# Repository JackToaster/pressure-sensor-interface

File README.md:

# Pressure Sensor Interface

This repository contains PCB designs & firmware (WIP) for an 8-channel USB pressure sensor/solenoid valve driver.

## Features

(Note that this is still in the early prototype stage so these specs have not been validated yet)

**8x pressure sensors**

- using the LWPxxx series of low-cost piezoresistive pressure sensors
- HX711 Load cell amplifier to read output
  - Note the full scale range of the pressure sensor is wider than the input range of the HX711 - This means the full range of the sensor may be impossible to read, but this is an acceptable tradeoff for the extremely low cost.
  - Capable of up to 144Hz sampling rate
 
**8x Solenoid Valve Drivers**

- Low-side NMOS switches
- Capable of ~4A per channel
- Separate DC power input for solenoid valves, supports 0-24VDC (Limited by 30V Vds rating of FET)
- Individual PWM control of each channel

**STM32F103 Microcontroller + USB-C**
idk

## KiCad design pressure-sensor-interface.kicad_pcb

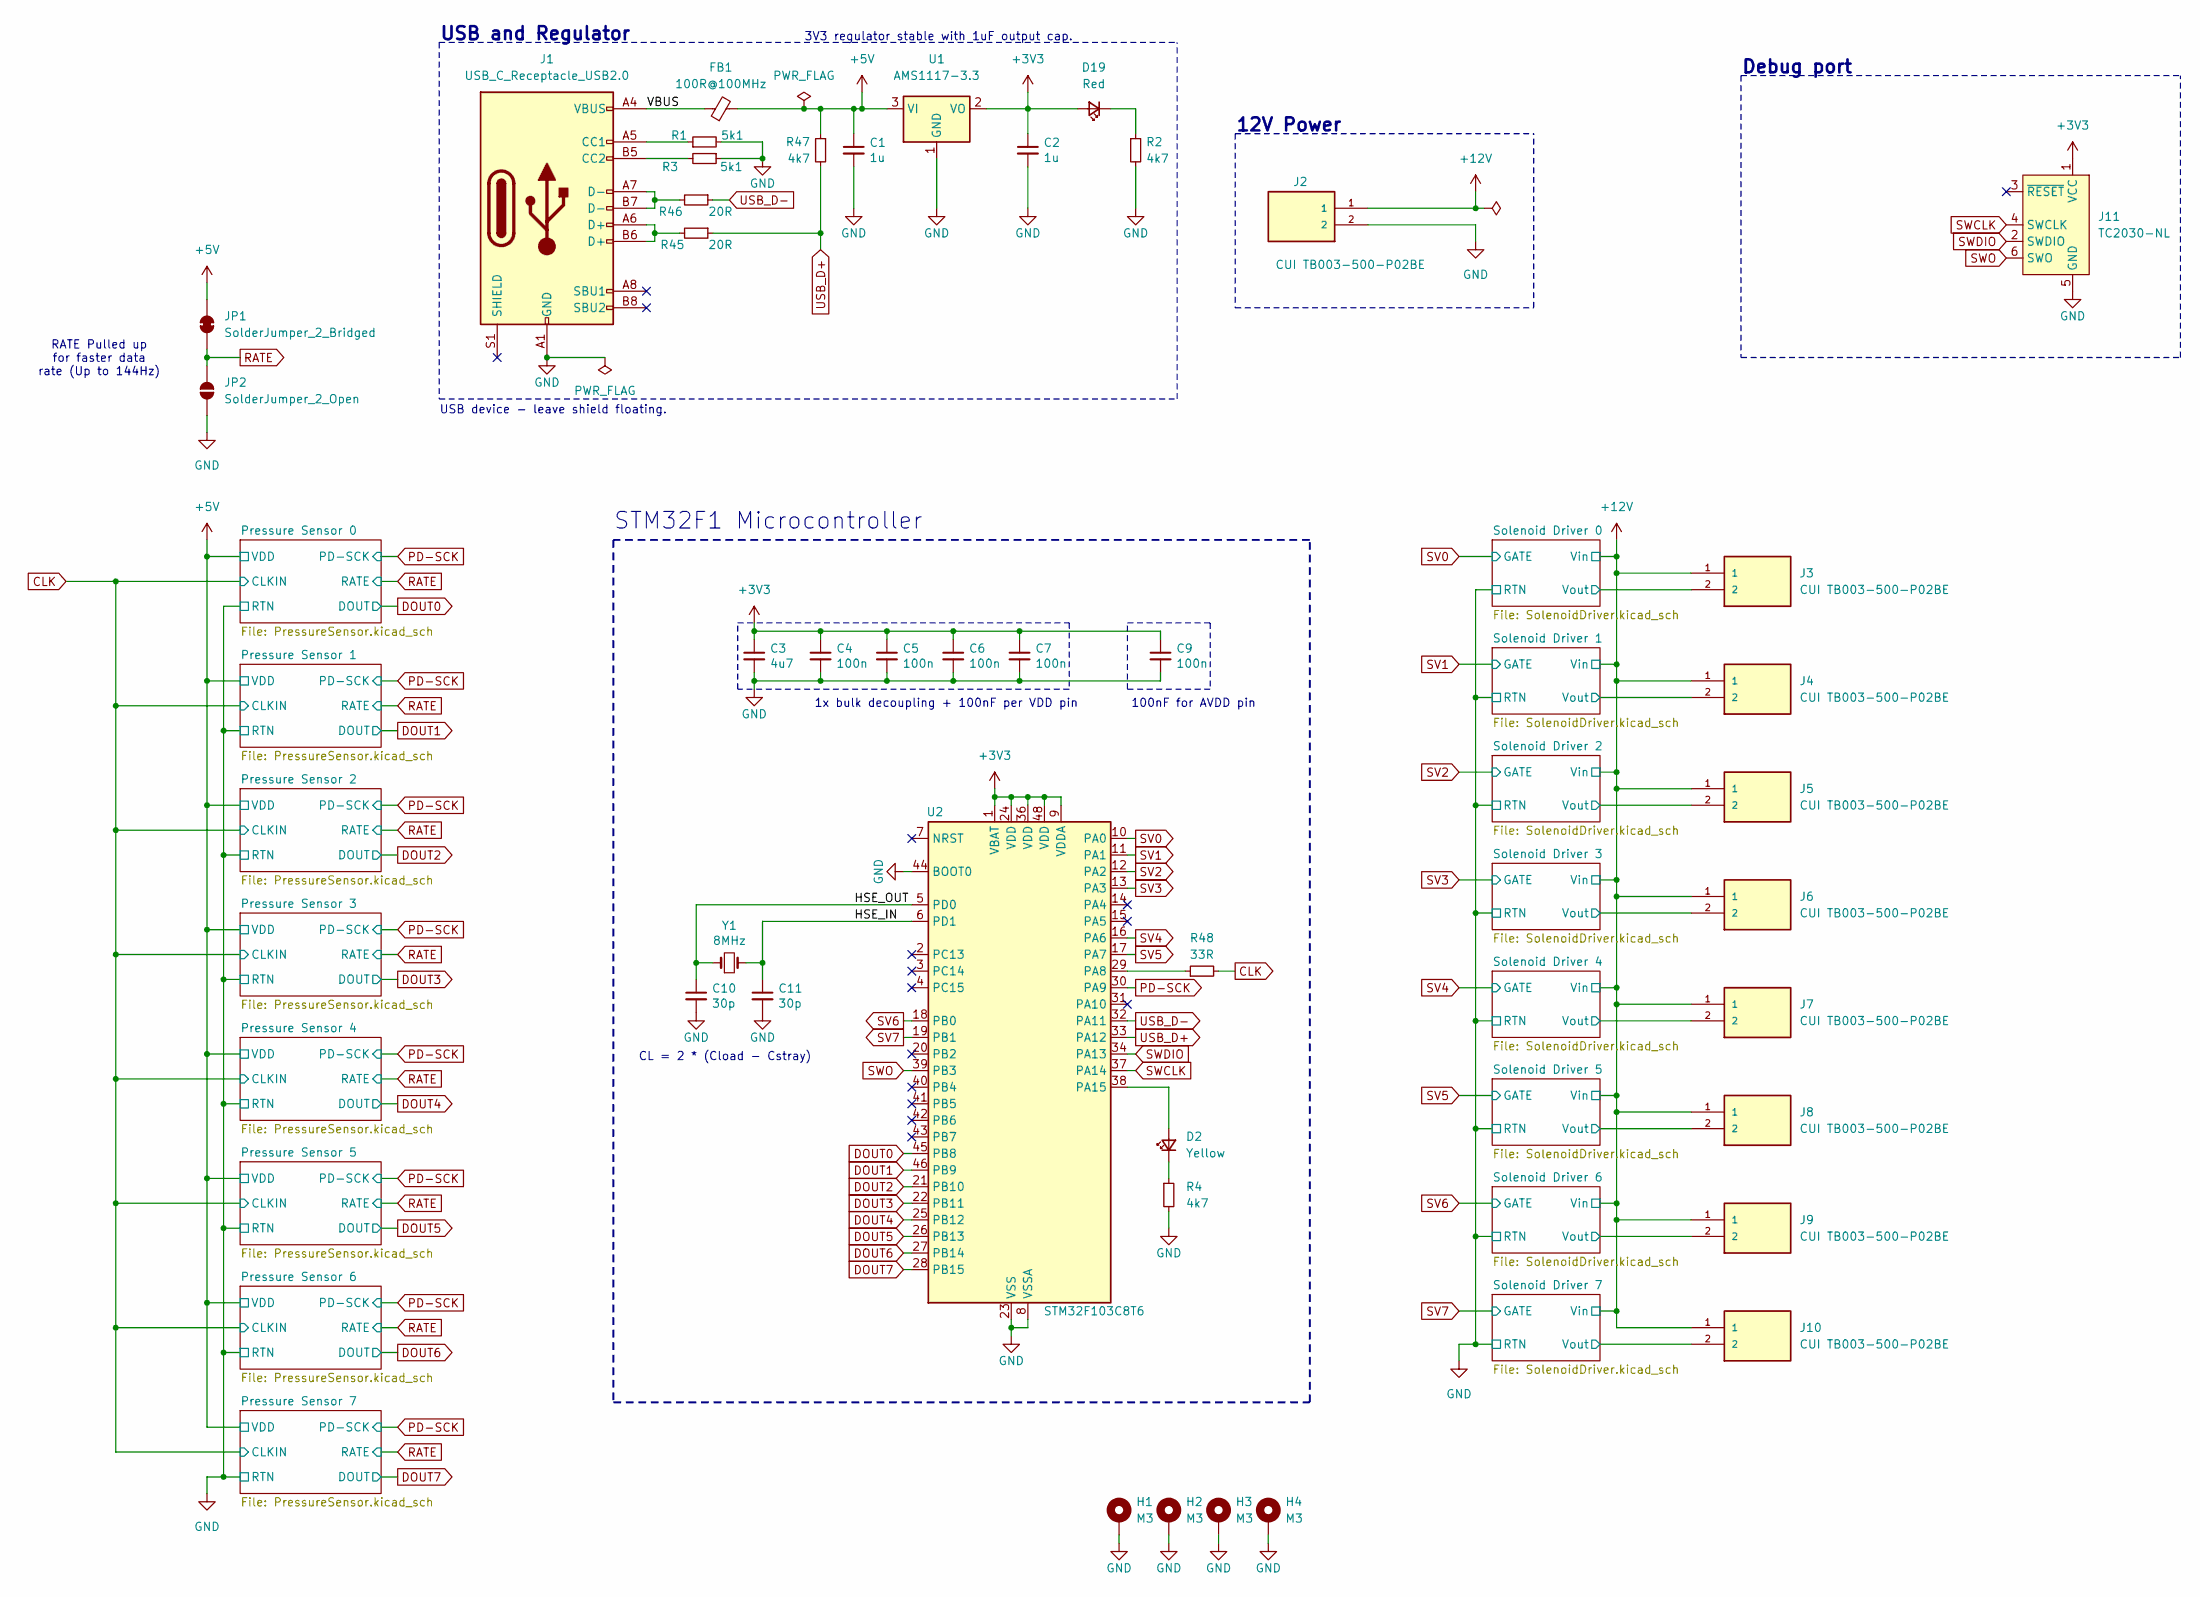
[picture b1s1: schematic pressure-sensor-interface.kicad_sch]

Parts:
C1, C2: 1u; C_0603_1608Metric; LCSC C15849
C3: 4u7; C_0603_1608Metric; LCSC C19666
C4, C5, C6, C7, C9: 100n; C_0603_1608Metric; LCSC C307331
C10, C11: 30p; C_0603_1608Metric; LCSC C1570
D2: Yellow; LED_0603_1608Metric
D19: Red; LED_0603_1608Metric
FB1: 100R@100MHz; R_0805_2012Metric; LCSC C1015
H1, H2, H3, H4: M3; MountingHole_2.2mm_M2_Pad_Via
J1: USB_C_Receptacle_USB2.0; USB_C_Receptacle_HRO_TYPE-C-31-M-12; LCSC C165948
J2, J3, J4, J5, J6, J7, J8, J9, J10: CUI TB003-500-P02BE; CUI_TB003-500-P02BE
J11: TC2030-NL; Tag-Connect_TC2030-IDC-NL_2x03_P1.27mm_Vertical
JP1: SolderJumper_2_Bridged; SolderJumper-2_P1.3mm_Bridged_Pad1.0x1.5mm
JP2: SolderJumper_2_Open; SolderJumper-2_P1.3mm_Open_TrianglePad1.0x1.5mm
R1, R3: 5k1; R_0603_1608Metric; LCSC C25905
R2, R4, R47: 4k7; R_0603_1608Metric
R45, R46: 20R; R_0603_1608Metric; LCSC C25905
R48: 33R; R_0603_1608Metric
U1: AMS1117-3.3; SOT-223-3_TabPin2; LCSC C6186
U2: STM32F103C8T6; LQFP-48_7x7mm_P0.5mm; LCSC C77994
Y1: 8MHz; Crystal_SMD_5032-2Pin_5.0x3.2mm; LCSC C115962

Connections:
+3V3: C2.1, C3.1, C4.1, C5.1, C6.1, C7.1, C9.1, D19.2 (A), J11.1 (VCC), U1.2 (VO), U2.1 (VBAT), U2.9 (VDDA), U2.24 (VDD), U2.36 (VDD), U2.48 (VDD)
+5V: C1.1, FB1.2, JP1.2 (B), R47.1, U1.3 (VI); also elsewhere on the board
+12V: J2.1, J3.1, J4.1, J5.1, J6.1, J7.1, J8.1, J9.1, J10.1; also elsewhere on the board
/HSE_IN: C11.1, U2.6 (PD1), Y1.2
/HSE_OUT: C10.1, U2.5 (PD0), Y1.1
/Solenoid Driver 0/Vout: J3.2; also elsewhere on the board
/Solenoid Driver 1/Vout: J4.2; also elsewhere on the board
/Solenoid Driver 2/Vout: J5.2; also elsewhere on the board
/Solenoid Driver 3/Vout: J6.2; also elsewhere on the board
/Solenoid Driver 4/Vout: J7.2; also elsewhere on the board
/Solenoid Driver 5/Vout: J8.2; also elsewhere on the board
/Solenoid Driver 6/Vout: J9.2; also elsewhere on the board
/Solenoid Driver 7/Vout: J10.2; also elsewhere on the board
/VBUS: FB1.1, J1.A4 (VBUS), J1.A9 (VBUS), J1.B4 (VBUS), J1.B9 (VBUS)
CLK: R48.2; also elsewhere on the board
DOUT0: U2.45 (PB8); also elsewhere on the board
DOUT1: U2.46 (PB9); also elsewhere on the board
DOUT2: U2.21 (PB10); also elsewhere on the board
DOUT3: U2.22 (PB11); also elsewhere on the board
DOUT4: U2.25 (PB12); also elsewhere on the board
DOUT5: U2.26 (PB13); also elsewhere on the board
DOUT6: U2.27 (PB14); also elsewhere on the board
DOUT7: U2.28 (PB15); also elsewhere on the board
GND: C1.2, C2.2, C3.2, C4.2, C5.2, C6.2, C7.2, C9.2, C10.2, C11.2, H1.1, H2.1, H3.1, H4.1, J1.A1 (GND), J1.A12 (GND), J1.B1 (GND), J1.B12 (GND), J2.2, J11.5 (GND), JP2.1 (A), R1.2, R2.2, R3.1, R4.2, U1.1 (GND), U2.8 (VSSA), U2.23 (VSS), U2.35 (VSS), U2.44 (BOOT0), U2.47 (VSS); also elsewhere on the board
unnamed: D2.2 (A), U2.38 (PA15)
unnamed: D2.1 (K), R4.1
unnamed: D19.1 (K), R2.1
unnamed: J1.A5 (CC1), R1.1
unnamed: J1.B5 (CC2), R3.2
unnamed: J1.A6 (D+), J1.B6 (D+), R45.2
unnamed: J1.A7 (D-), J1.B7 (D-), R46.2
unnamed: R48.1, U2.29 (PA8)
PD-SCK: U2.30 (PA9); also elsewhere on the board
RATE: JP1.1 (A), JP2.2 (B); also elsewhere on the board
SV0: U2.10 (PA0); also elsewhere on the board
SV1: U2.11 (PA1); also elsewhere on the board
SV2: U2.12 (PA2); also elsewhere on the board
SV3: U2.13 (PA3); also elsewhere on the board
SV4: U2.16 (PA6); also elsewhere on the board
SV5: U2.17 (PA7); also elsewhere on the board
SV6: U2.18 (PB0); also elsewhere on the board
SV7: U2.19 (PB1); also elsewhere on the board
SWCLK: J11.4 (SWCLK), U2.37 (PA14)
SWDIO: J11.2 (SWDIO), U2.34 (PA13)
SWO: J11.6 (SWO), U2.39 (PB3)
USB_D+: R45.1, R47.2, U2.33 (PA12)
USB_D-: R46.1, U2.32 (PA11)

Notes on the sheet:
12V Power
Debug port
USB and Regulator
3V3 regulator stable with 1uF output cap.
RATE Pulled up for faster data rate (Up to 144Hz)
100nF for AVDD pin
1x bulk decoupling + 100nF per VDD pin
CL = 2 * (Cload - Cstray)
STM32F1 Microcontroller
USB device - leave shield floating.

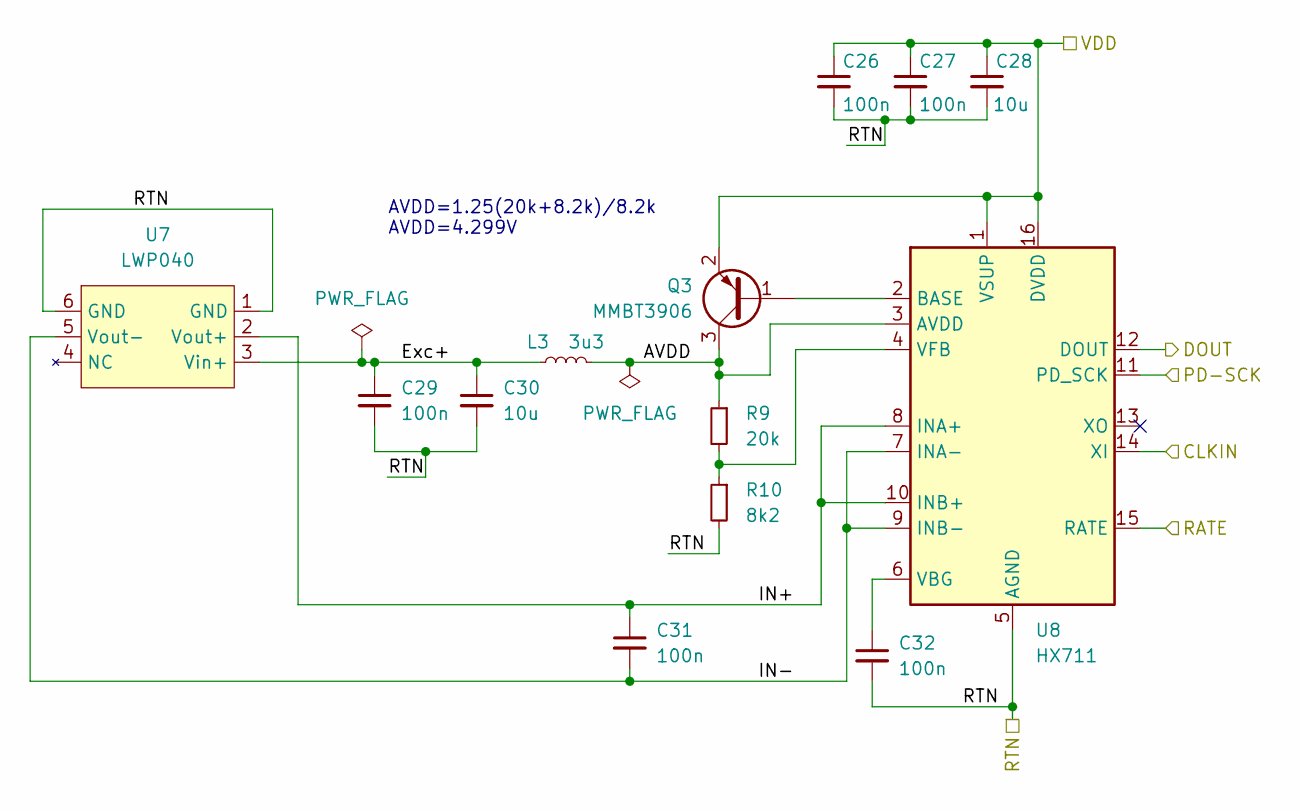
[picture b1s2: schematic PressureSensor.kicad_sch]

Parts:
C26, C27, C29, C31, C32: 100n; C_0603_1608Metric
C28, C30: 10u; C_0603_1608Metric
L3: 3u3; L_0603_1608Metric
Q3: MMBT3906; SOT-23
R9: 20k; R_0603_1608Metric
R10: 8k2; R_0603_1608Metric
U7: LWP040; SOIC-6-Pressure-Sensor
U8: HX711; SOP-16_3.9x9.9mm_P1.27mm

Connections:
+5V: C26.1, C27.1, C28.1, Q3.2 (E), U8.1 (VSUP), U8.16 (DVDD); also elsewhere on the board
/Pressure Sensor 2/AVDD: L3.2, Q3.3 (C), R9.1, U8.3 (AVDD)
/Pressure Sensor 2/Exc+: C29.1, C30.1, L3.1, U7.3 (Vin+)
/Pressure Sensor 2/IN+: C31.1, U7.2 (Vout+), U8.8 (INA+), U8.10 (INB+)
/Pressure Sensor 2/IN-: C31.2, U7.5 (Vout-), U8.7 (INA-), U8.9 (INB-)
CLK: U8.14 (XI); also elsewhere on the board
DOUT2: U8.12 (DOUT); also elsewhere on the board
GND: C26.2, C27.2, C28.2, C29.2, C30.2, C32.2, R10.2, U7.1 (GND), U7.6 (GND), U8.5 (AGND); also elsewhere on the board
unnamed: Q3.1 (B), U8.2 (BASE)
unnamed: C32.1, U8.6 (VBG)
unnamed: R9.2, R10.1, U8.4 (VFB)
PD-SCK: U8.11 (PD_SCK); also elsewhere on the board
RATE: U8.15 (RATE); also elsewhere on the board

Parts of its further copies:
C12, C13, C15, C17, C18, C19, C20, C22, C24, C25, C33, C34, C36, C38, C39, C40, C41, C43, C45, C46, C47, C48, C50, C52, C53, C54, C55, C57, C59, C60, C61, C62, C64, C66, C67: 100n; C_0603_1608Metric
C14, C16, C21, C23, C35, C37, C42, C44, C49, C51, C56, C58, C63, C65: 10u; C_0603_1608Metric
L1, L2, L4, L5, L6, L7, L8: 3u3; L_0603_1608Metric
Q1, Q2, Q4, Q5, Q6, Q7, Q8: MMBT3906; SOT-23
R5, R7, R11, R13, R15, R17, R19: 20k; R_0603_1608Metric
R6, R8, R12, R14, R16, R18, R20: 8k2; R_0603_1608Metric
U3, U5, U9, U11, U13, U15, U17: LWP040; SOIC-6-Pressure-Sensor
U4, U6, U10, U12, U14, U16, U18: HX711; SOP-16_3.9x9.9mm_P1.27mm

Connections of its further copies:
+5V: C12.1, C13.1, C14.1, C19.1, C20.1, C21.1, C33.1, C34.1, C35.1, C40.1, C41.1, C42.1, C47.1, C48.1, C49.1, C54.1, C55.1, C56.1, C61.1, C62.1, C63.1, Q1.2 (E), Q2.2 (E), Q4.2 (E), Q5.2 (E), Q6.2 (E), Q7.2 (E), Q8.2 (E), U4.1 (VSUP), U4.16 (DVDD), U6.1 (VSUP), U6.16 (DVDD), U10.1 (VSUP), U10.16 (DVDD), U12.1 (VSUP), U12.16 (DVDD), U14.1 (VSUP), U14.16 (DVDD), U16.1 (VSUP), U16.16 (DVDD), U18.1 (VSUP), U18.16 (DVDD); also elsewhere on the board
/Pressure Sensor 0/AVDD: L1.2, Q1.3 (C), R5.1, U4.3 (AVDD)
/Pressure Sensor 0/Exc+: C15.1, C16.1, L1.1, U3.3 (Vin+)
/Pressure Sensor 0/IN+: C17.1, U3.2 (Vout+), U4.8 (INA+), U4.10 (INB+)
/Pressure Sensor 0/IN-: C17.2, U3.5 (Vout-), U4.7 (INA-), U4.9 (INB-)
/Pressure Sensor 1/AVDD: L2.2, Q2.3 (C), R7.1, U6.3 (AVDD)
/Pressure Sensor 1/Exc+: C22.1, C23.1, L2.1, U5.3 (Vin+)
/Pressure Sensor 1/IN+: C24.1, U5.2 (Vout+), U6.8 (INA+), U6.10 (INB+)
/Pressure Sensor 1/IN-: C24.2, U5.5 (Vout-), U6.7 (INA-), U6.9 (INB-)
/Pressure Sensor 3/AVDD: L4.2, Q4.3 (C), R11.1, U10.3 (AVDD)
/Pressure Sensor 3/Exc+: C36.1, C37.1, L4.1, U9.3 (Vin+)
/Pressure Sensor 3/IN+: C38.1, U9.2 (Vout+), U10.8 (INA+), U10.10 (INB+)
/Pressure Sensor 3/IN-: C38.2, U9.5 (Vout-), U10.7 (INA-), U10.9 (INB-)
/Pressure Sensor 4/AVDD: L5.2, Q5.3 (C), R13.1, U12.3 (AVDD)
/Pressure Sensor 4/Exc+: C43.1, C44.1, L5.1, U11.3 (Vin+)
/Pressure Sensor 4/IN+: C45.1, U11.2 (Vout+), U12.8 (INA+), U12.10 (INB+)
/Pressure Sensor 4/IN-: C45.2, U11.5 (Vout-), U12.7 (INA-), U12.9 (INB-)
/Pressure Sensor 5/AVDD: L6.2, Q6.3 (C), R15.1, U14.3 (AVDD)
/Pressure Sensor 5/Exc+: C50.1, C51.1, L6.1, U13.3 (Vin+)
/Pressure Sensor 5/IN+: C52.1, U13.2 (Vout+), U14.8 (INA+), U14.10 (INB+)
/Pressure Sensor 5/IN-: C52.2, U13.5 (Vout-), U14.7 (INA-), U14.9 (INB-)
/Pressure Sensor 6/AVDD: L7.2, Q7.3 (C), R17.1, U16.3 (AVDD)
/Pressure Sensor 6/Exc+: C57.1, C58.1, L7.1, U15.3 (Vin+)
/Pressure Sensor 6/IN+: C59.1, U15.2 (Vout+), U16.8 (INA+), U16.10 (INB+)
/Pressure Sensor 6/IN-: C59.2, U15.5 (Vout-), U16.7 (INA-), U16.9 (INB-)
/Pressure Sensor 7/AVDD: L8.2, Q8.3 (C), R19.1, U18.3 (AVDD)
/Pressure Sensor 7/Exc+: C64.1, C65.1, L8.1, U17.3 (Vin+)
/Pressure Sensor 7/IN+: C66.1, U17.2 (Vout+), U18.8 (INA+), U18.10 (INB+)
/Pressure Sensor 7/IN-: C66.2, U17.5 (Vout-), U18.7 (INA-), U18.9 (INB-)
CLK: U4.14 (XI), U6.14 (XI), U10.14 (XI), U12.14 (XI), U14.14 (XI), U16.14 (XI), U18.14 (XI); also elsewhere on the board
DOUT0: U4.12 (DOUT); also elsewhere on the board
DOUT1: U6.12 (DOUT); also elsewhere on the board
DOUT3: U10.12 (DOUT); also elsewhere on the board
DOUT4: U12.12 (DOUT); also elsewhere on the board
DOUT5: U14.12 (DOUT); also elsewhere on the board
DOUT6: U16.12 (DOUT); also elsewhere on the board
DOUT7: U18.12 (DOUT); also elsewhere on the board
GND: C12.2, C13.2, C14.2, C15.2, C16.2, C18.2, C19.2, C20.2, C21.2, C22.2, C23.2, C25.2, C33.2, C34.2, C35.2, C36.2, C37.2, C39.2, C40.2, C41.2, C42.2, C43.2, C44.2, C46.2, C47.2, C48.2, C49.2, C50.2, C51.2, C53.2, C54.2, C55.2, C56.2, C57.2, C58.2, C60.2, C61.2, C62.2, C63.2, C64.2, C65.2, C67.2, R6.2, R8.2, R12.2, R14.2, R16.2, R18.2, R20.2, U3.1 (GND), U3.6 (GND), U4.5 (AGND), U5.1 (GND), U5.6 (GND), U6.5 (AGND), U9.1 (GND), U9.6 (GND), U10.5 (AGND), U11.1 (GND), U11.6 (GND), U12.5 (AGND), U13.1 (GND), U13.6 (GND), U14.5 (AGND), U15.1 (GND), U15.6 (GND), U16.5 (AGND), U17.1 (GND), U17.6 (GND), U18.5 (AGND); also elsewhere on the board
unnamed: Q1.1 (B), U4.2 (BASE)
unnamed: Q2.1 (B), U6.2 (BASE)
unnamed: Q4.1 (B), U10.2 (BASE)
unnamed: Q5.1 (B), U12.2 (BASE)
unnamed: Q6.1 (B), U14.2 (BASE)
unnamed: Q7.1 (B), U16.2 (BASE)
unnamed: Q8.1 (B), U18.2 (BASE)
unnamed: C18.1, U4.6 (VBG)
unnamed: R5.2, R6.1, U4.4 (VFB)
unnamed: C25.1, U6.6 (VBG)
unnamed: R7.2, R8.1, U6.4 (VFB)
unnamed: C39.1, U10.6 (VBG)
unnamed: R11.2, R12.1, U10.4 (VFB)
unnamed: C46.1, U12.6 (VBG)
unnamed: R13.2, R14.1, U12.4 (VFB)
unnamed: C53.1, U14.6 (VBG)
unnamed: R15.2, R16.1, U14.4 (VFB)
unnamed: C60.1, U16.6 (VBG)
unnamed: R17.2, R18.1, U16.4 (VFB)
unnamed: C67.1, U18.6 (VBG)
unnamed: R19.2, R20.1, U18.4 (VFB)
PD-SCK: U4.11 (PD_SCK), U6.11 (PD_SCK), U10.11 (PD_SCK), U12.11 (PD_SCK), U14.11 (PD_SCK), U16.11 (PD_SCK), U18.11 (PD_SCK); also elsewhere on the board
RATE: U4.15 (RATE), U6.15 (RATE), U10.15 (RATE), U12.15 (RATE), U14.15 (RATE), U16.15 (RATE), U18.15 (RATE); also elsewhere on the board

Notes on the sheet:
AVDD=1.25(20k+8.2k)/8.2k AVDD=4.299V

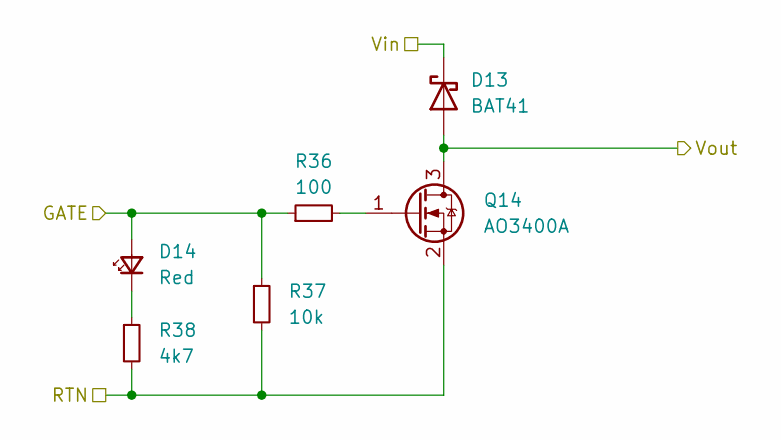
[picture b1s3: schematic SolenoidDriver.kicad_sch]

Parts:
D13: BAT41; D_SOD-123
D14: Red; LED_0603_1608Metric
Q14: AO3400A; SOT-23
R36: 100; R_0603_1608Metric
R37: 10k; R_0603_1608Metric
R38: 4k7; R_0603_1608Metric

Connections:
+12V: D13.1 (K); also elsewhere on the board
/Solenoid Driver 5/Vout: D13.2 (A), Q14.3 (D); also elsewhere on the board
GND: Q14.2 (S), R37.2, R38.2; also elsewhere on the board
unnamed: D14.1 (K), R38.1
unnamed: Q14.1 (G), R36.2
SV5: D14.2 (A), R36.1, R37.1; also elsewhere on the board

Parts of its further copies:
D3, D5, D7, D9, D11, D15, D17: BAT41; D_SOD-123
D4, D6, D8, D10, D12, D16, D18: Red; LED_0603_1608Metric
Q9, Q10, Q11, Q12, Q13, Q15, Q16: AO3400A; SOT-23
R21, R24, R27, R30, R33, R39, R42: 100; R_0603_1608Metric
R22, R25, R28, R31, R34, R40, R43: 10k; R_0603_1608Metric
R23, R26, R29, R32, R35, R41, R44: 4k7; R_0603_1608Metric

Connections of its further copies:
+12V: D3.1 (K), D5.1 (K), D7.1 (K), D9.1 (K), D11.1 (K), D15.1 (K), D17.1 (K); also elsewhere on the board
/Solenoid Driver 0/Vout: D3.2 (A), Q9.3 (D); also elsewhere on the board
/Solenoid Driver 1/Vout: D5.2 (A), Q10.3 (D); also elsewhere on the board
/Solenoid Driver 2/Vout: D7.2 (A), Q11.3 (D); also elsewhere on the board
/Solenoid Driver 3/Vout: D9.2 (A), Q12.3 (D); also elsewhere on the board
/Solenoid Driver 4/Vout: D11.2 (A), Q13.3 (D); also elsewhere on the board
/Solenoid Driver 6/Vout: D15.2 (A), Q15.3 (D); also elsewhere on the board
/Solenoid Driver 7/Vout: D17.2 (A), Q16.3 (D); also elsewhere on the board
GND: Q9.2 (S), Q10.2 (S), Q11.2 (S), Q12.2 (S), Q13.2 (S), Q15.2 (S), Q16.2 (S), R22.2, R23.2, R25.2, R26.2, R28.2, R29.2, R31.2, R32.2, R34.2, R35.2, R40.2, R41.2, R43.2, R44.2; also elsewhere on the board
unnamed: D4.1 (K), R23.1
unnamed: D6.1 (K), R26.1
unnamed: D8.1 (K), R29.1
unnamed: D10.1 (K), R32.1
unnamed: D12.1 (K), R35.1
unnamed: D16.1 (K), R41.1
unnamed: D18.1 (K), R44.1
unnamed: Q9.1 (G), R21.2
unnamed: Q10.1 (G), R24.2
unnamed: Q11.1 (G), R27.2
unnamed: Q12.1 (G), R30.2
unnamed: Q13.1 (G), R33.2
unnamed: Q15.1 (G), R39.2
unnamed: Q16.1 (G), R42.2
SV0: D4.2 (A), R21.1, R22.1; also elsewhere on the board
SV1: D6.2 (A), R24.1, R25.1; also elsewhere on the board
SV2: D8.2 (A), R27.1, R28.1; also elsewhere on the board
SV3: D10.2 (A), R30.1, R31.1; also elsewhere on the board
SV4: D12.2 (A), R33.1, R34.1; also elsewhere on the board
SV6: D16.2 (A), R39.1, R40.1; also elsewhere on the board
SV7: D18.2 (A), R42.1, R43.1; also elsewhere on the board

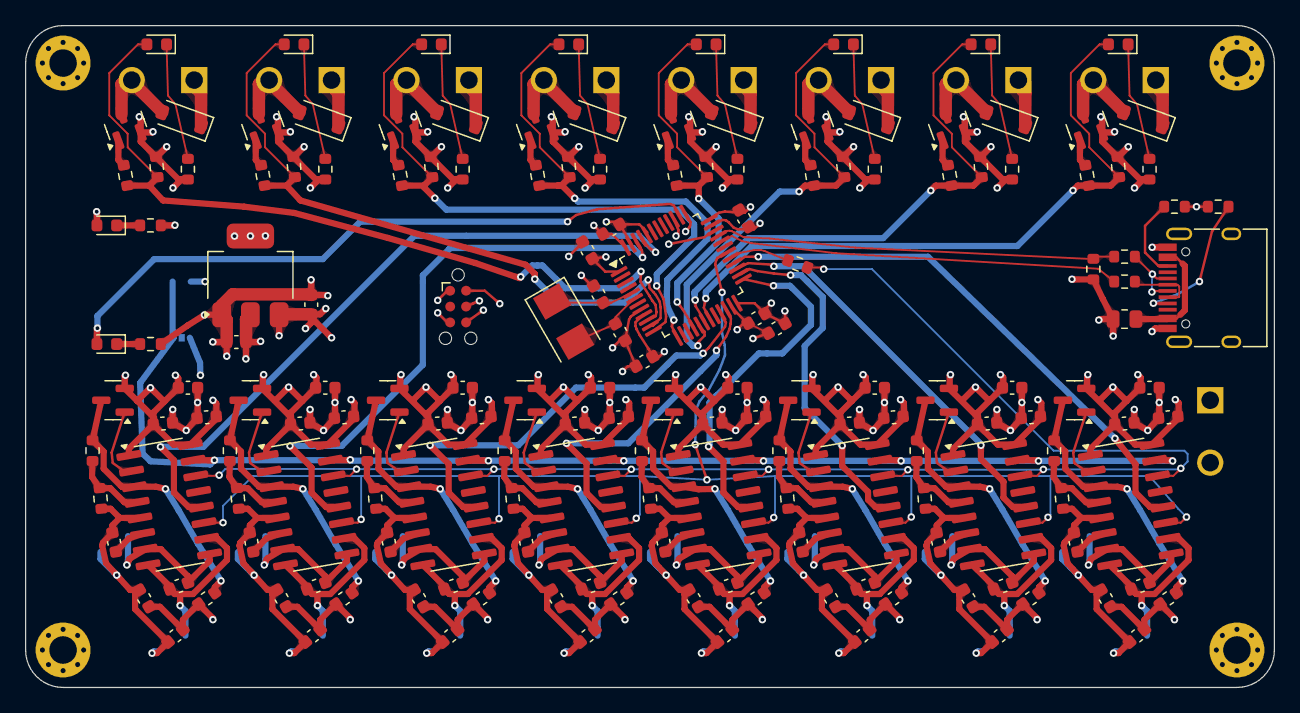
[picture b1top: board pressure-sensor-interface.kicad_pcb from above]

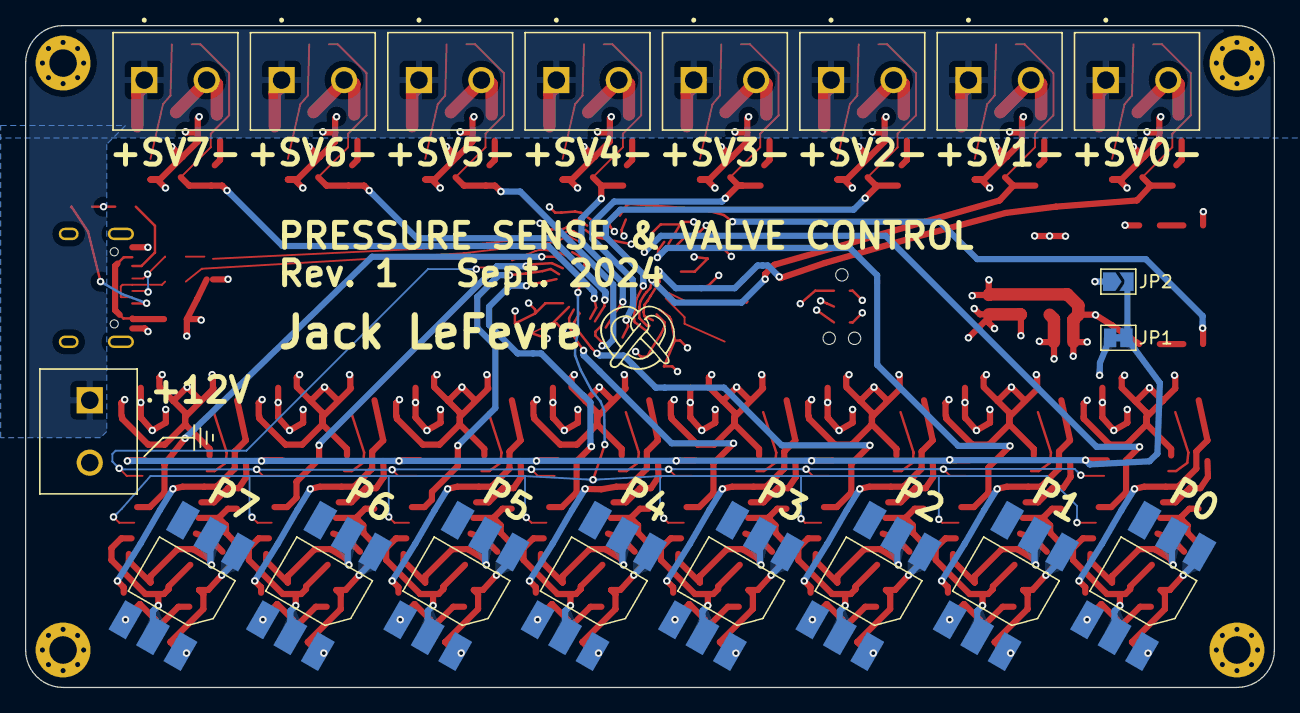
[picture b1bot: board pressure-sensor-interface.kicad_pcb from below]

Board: 4 copper layers, 100.0 x 53.0 mm, 193 parts (19 on the bottom side), 119 nets.

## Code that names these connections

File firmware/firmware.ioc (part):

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Mcu.Name=STM32F103C(8-B)Tx
Mcu.Package=LQFP48
Mcu.UserName=STM32F103C8Tx
PA0-WKUP.Signal=S_TIM2_CH1_ETR
PA1.Signal=S_TIM2_CH2
PA11.Mode=Device
PA11.Signal=USB_DM
PA12.Mode=Device
PA12.Signal=USB_DP
PA13.Mode=Trace_Asynchronous_SW
PA13.Signal=SYS_JTMS-SWDIO
PA14.Mode=Trace_Asynchronous_SW
PA14.Signal=SYS_JTCK-SWCLK
PA2.Signal=S_TIM2_CH3
PA3.Signal=S_TIM2_CH4
PA6.Signal=S_TIM3_CH1
PA7.Signal=S_TIM3_CH2
PA8.GPIOParameters=GPIO_Label
PA8.GPIO_Label=CLK
PA8.Signal=S_TIM1_CH1
PA9.GPIOParameters=GPIO_Label
PA9.GPIO_Label=PD-SCK
PA9.Signal=GPIO_Output
PB0.Signal=S_TIM3_CH3
PB1.Signal=S_TIM3_CH4
PB10.GPIOParameters=GPIO_Label
PB10.GPIO_Label=DOUT2
PB10.Signal=GPIO_Input
PB11.GPIOParameters=GPIO_Label
PB11.GPIO_Label=DOUT3
PB11.Signal=GPIO_Input
PB12.GPIOParameters=GPIO_Label
PB12.GPIO_Label=DOUT4
PB12.Signal=GPIO_Input
PB13.GPIOParameters=GPIO_Label
PB13.GPIO_Label=DOUT5
PB13.Signal=GPIO_Input
PB14.GPIOParameters=GPIO_Label
PB14.GPIO_Label=DOUT6
PB14.Signal=GPIO_Input
PB15.GPIOParameters=GPIO_Label
PB15.GPIO_Label=DOUT7
PB15.Signal=GPIO_Input
PB3.Mode=Trace_Asynchronous_SW
PB3.Signal=SYS_JTDO-TRACESWO
PB8.GPIOParameters=GPIO_Label
PB8.GPIO_Label=DOUT0
PB8.Signal=GPIO_Input
PB9.GPIOParameters=GPIO_Label
PB9.GPIO_Label=DOUT1
PB9.Signal=GPIO_Input
PD0-OSC_IN.Mode=HSE-External-Oscillator
PD0-OSC_IN.Signal=RCC_OSC_IN
PD1-OSC_OUT.Mode=HSE-External-Oscillator
PD1-OSC_OUT.Signal=RCC_OSC_OUT
RCC.SYSCLKFreq_VALUE=72000000
RCC.SYSCLKSource=RCC_SYSCLKSOURCE_PLLCLK
board=custom

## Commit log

2024-09-08 initial commit, created layout
2024-09-09 create kibot ci action from template
2024-09-09 test
2024-09-09 Update kibot.yml again
2024-09-09 Update kibot.yml to use quick start
2024-09-09 fix typo in kibot.yml
2024-09-09 Update kibot.yml yet again
2024-11-11 usb cdc firmware start
2024-11-11 add requirements.txt for host sw
2024-11-12 clean up gitignore, start host gui
2024-11-12 host gui work
2024-11-17 test valve control
2024-11-28 Read data from serial, update rate adjustment
2024-11-30 added manual and auto valve control
